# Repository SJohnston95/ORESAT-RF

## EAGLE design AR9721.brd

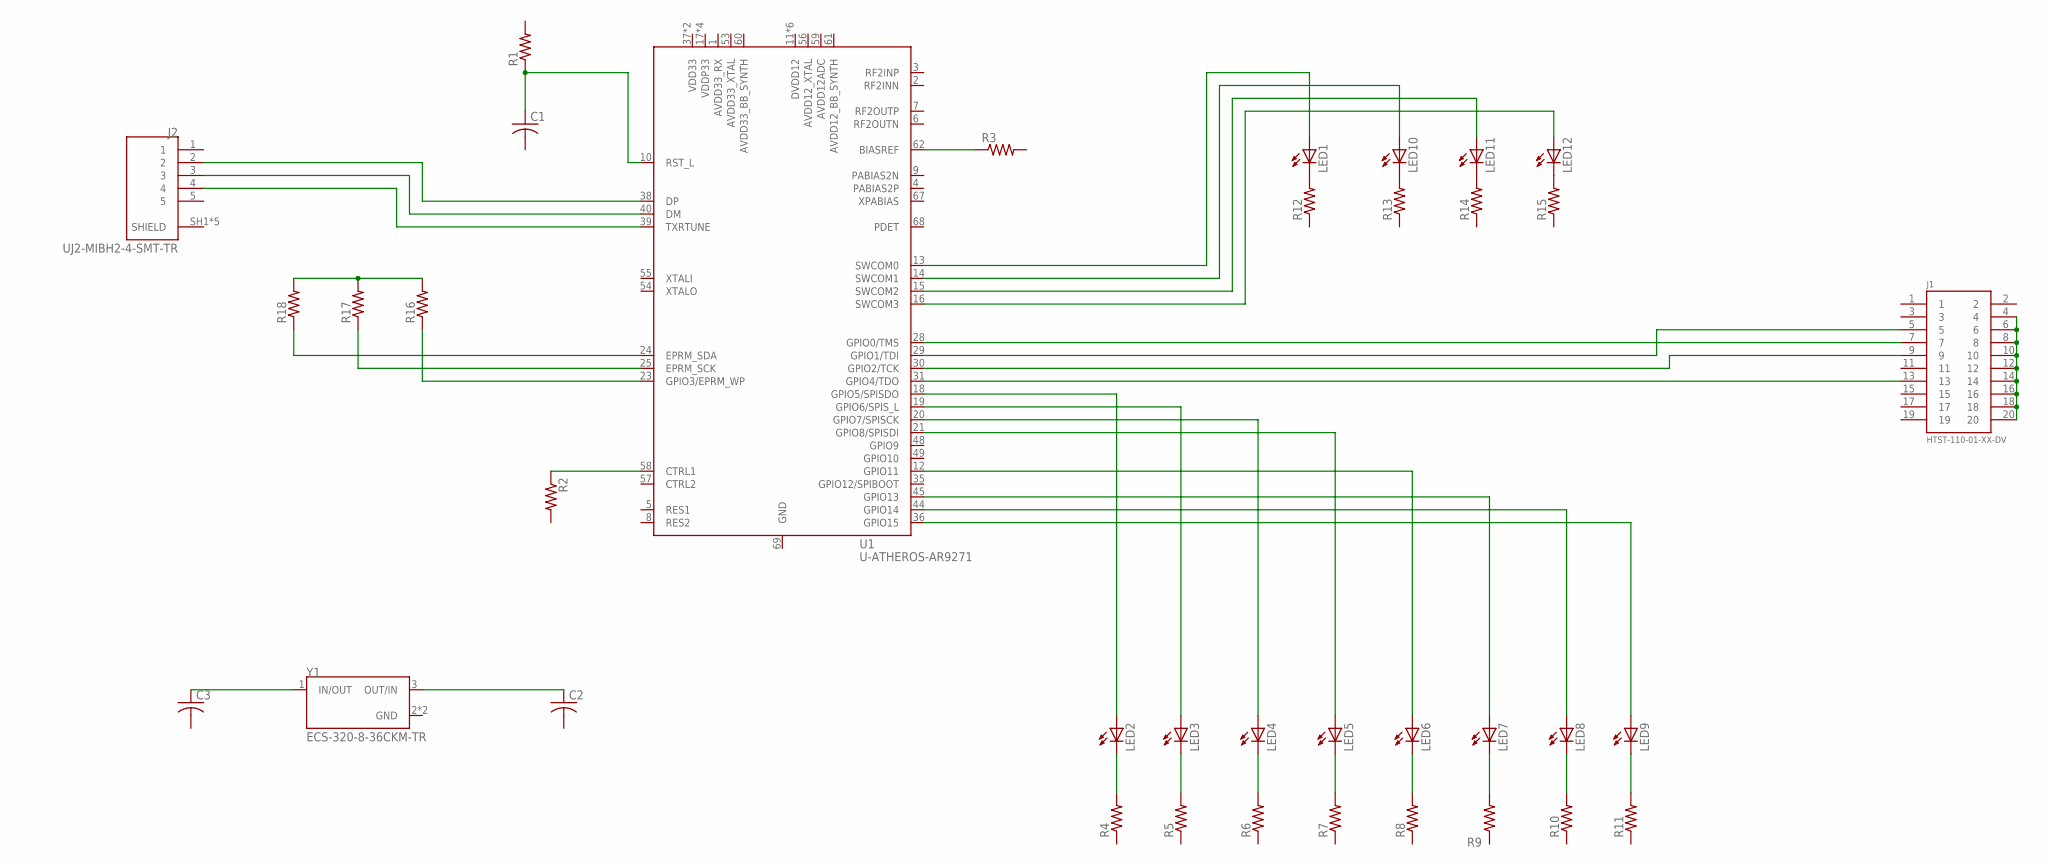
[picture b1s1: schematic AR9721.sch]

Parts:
C1, C2, C3: C-USC0603; C0603
J1: HTST-110-01-XX-DV
J2: UJ2-MIBH2-4-SMT-TR; CUI_UJ2-MIBH2-4-SMT-TR
LED1, LED2, LED3, LED4, LED5, LED6, LED7, LED8, LED9, LED10, LED11, LED12: LEDCHIP-LED0603; CHIP-LED0603
R1, R2, R3, R4, R5, R6, R7, R8, R9, R10, R11, R12, R13, R14, R15, R16, R17, R18: R-US_R0603; R0603
U1: U-ATHEROS-AR9271; QFN-68
Y1: ECS-320-8-36CKM-TR; XTAL_ECS-160-10-36-JGN-TR

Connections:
AVDD12ADC: U1.59 (AVDD12ADC)
AVDD12_BB_SYNTH: U1.61 (AVDD12_BB_SYNTH)
AVDD12_XTAL: U1.56 (AVDD12_XTAL)
AVDD33_BB_SYNTH: U1.60 (AVDD33_BB_SYNTH)
AVDD33_RX: U1.1 (AVDD33_RX)
AVDD33_XTAL: U1.53 (AVDD33_XTAL)
DVDD12: U1.11 (DVDD12), U1.22 (DVDD12), U1.27 (DVDD12), U1.42 (DVDD12), U1.43 (DVDD12), U1.46 (DVDD12)
GND: U1.69 (GND), Y1.2 (GND), Y1.4 (GND)
unnamed: LED2.A, U1.18 (GPIO5/SPISDO)
unnamed: LED3.A, U1.19 (GPIO6/SPIS_L)
unnamed: LED4.A, U1.20 (GPIO7/SPISCK)
unnamed: LED5.A, U1.21 (GPIO8/SPISDI)
unnamed: LED6.A, U1.12 (GPIO11)
unnamed: LED7.A, U1.45 (GPIO13)
unnamed: LED8.A, U1.44 (GPIO14)
unnamed: LED9.A, U1.36 (GPIO15)
unnamed: LED2.C, R4.2
unnamed: LED3.C, R5.2
unnamed: LED4.C, R6.2
unnamed: LED5.C, R7.2
unnamed: LED6.C, R8.2
unnamed: LED7.C, R9.2
unnamed: LED8.C, R10.2
unnamed: LED9.C, R11.2
unnamed: LED1.A, U1.13 (SWCOM0)
unnamed: LED10.A, U1.14 (SWCOM1)
unnamed: LED11.A, U1.15 (SWCOM2)
unnamed: LED12.A, U1.16 (SWCOM3)
unnamed: LED1.C, R12.2
unnamed: LED10.C, R13.2
unnamed: LED11.C, R14.2
unnamed: LED12.C, R15.2
unnamed: R2.1, U1.58 (CTRL1)
unnamed: R16.2, R17.2, R18.2
unnamed: R16.1, U1.23 (GPIO3/EPRM_WP)
unnamed: R17.1, U1.25 (EPRM_SCK)
unnamed: R18.1, U1.24 (EPRM_SDA)
unnamed: R3.1, U1.62 (BIASREF)
unnamed: C1.1, R1.1, U1.10 (RST_L)
unnamed: C2.1, Y1.3 (OUT/IN)
unnamed: C3.1, Y1.1 (IN/OUT)
unnamed: J2.2, U1.38 (DP)
unnamed: J2.3, U1.40 (DM)
unnamed: J2.4, U1.39 (TXRTUNE)
unnamed: J1.7, U1.28 (GPIO0/TMS)
unnamed: J1.5, U1.29 (GPIO1/TDI)
unnamed: J1.9, U1.30 (GPIO2/TCK)
unnamed: J1.13, U1.31 (GPIO4/TDO)
unnamed: J1.4, J1.6, J1.8, J1.10, J1.12, J1.14, J1.16, J1.18, J1.20
VDD33: U1.37 (VDD33), U1.41 (VDD33)
VDDP33: U1.17 (VDDP33), U1.26 (VDDP33), U1.33 (VDDP33), U1.47 (VDDP33)

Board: 2 copper layers, 37 parts (0 on the bottom side), 45 nets, no tracks yet.
